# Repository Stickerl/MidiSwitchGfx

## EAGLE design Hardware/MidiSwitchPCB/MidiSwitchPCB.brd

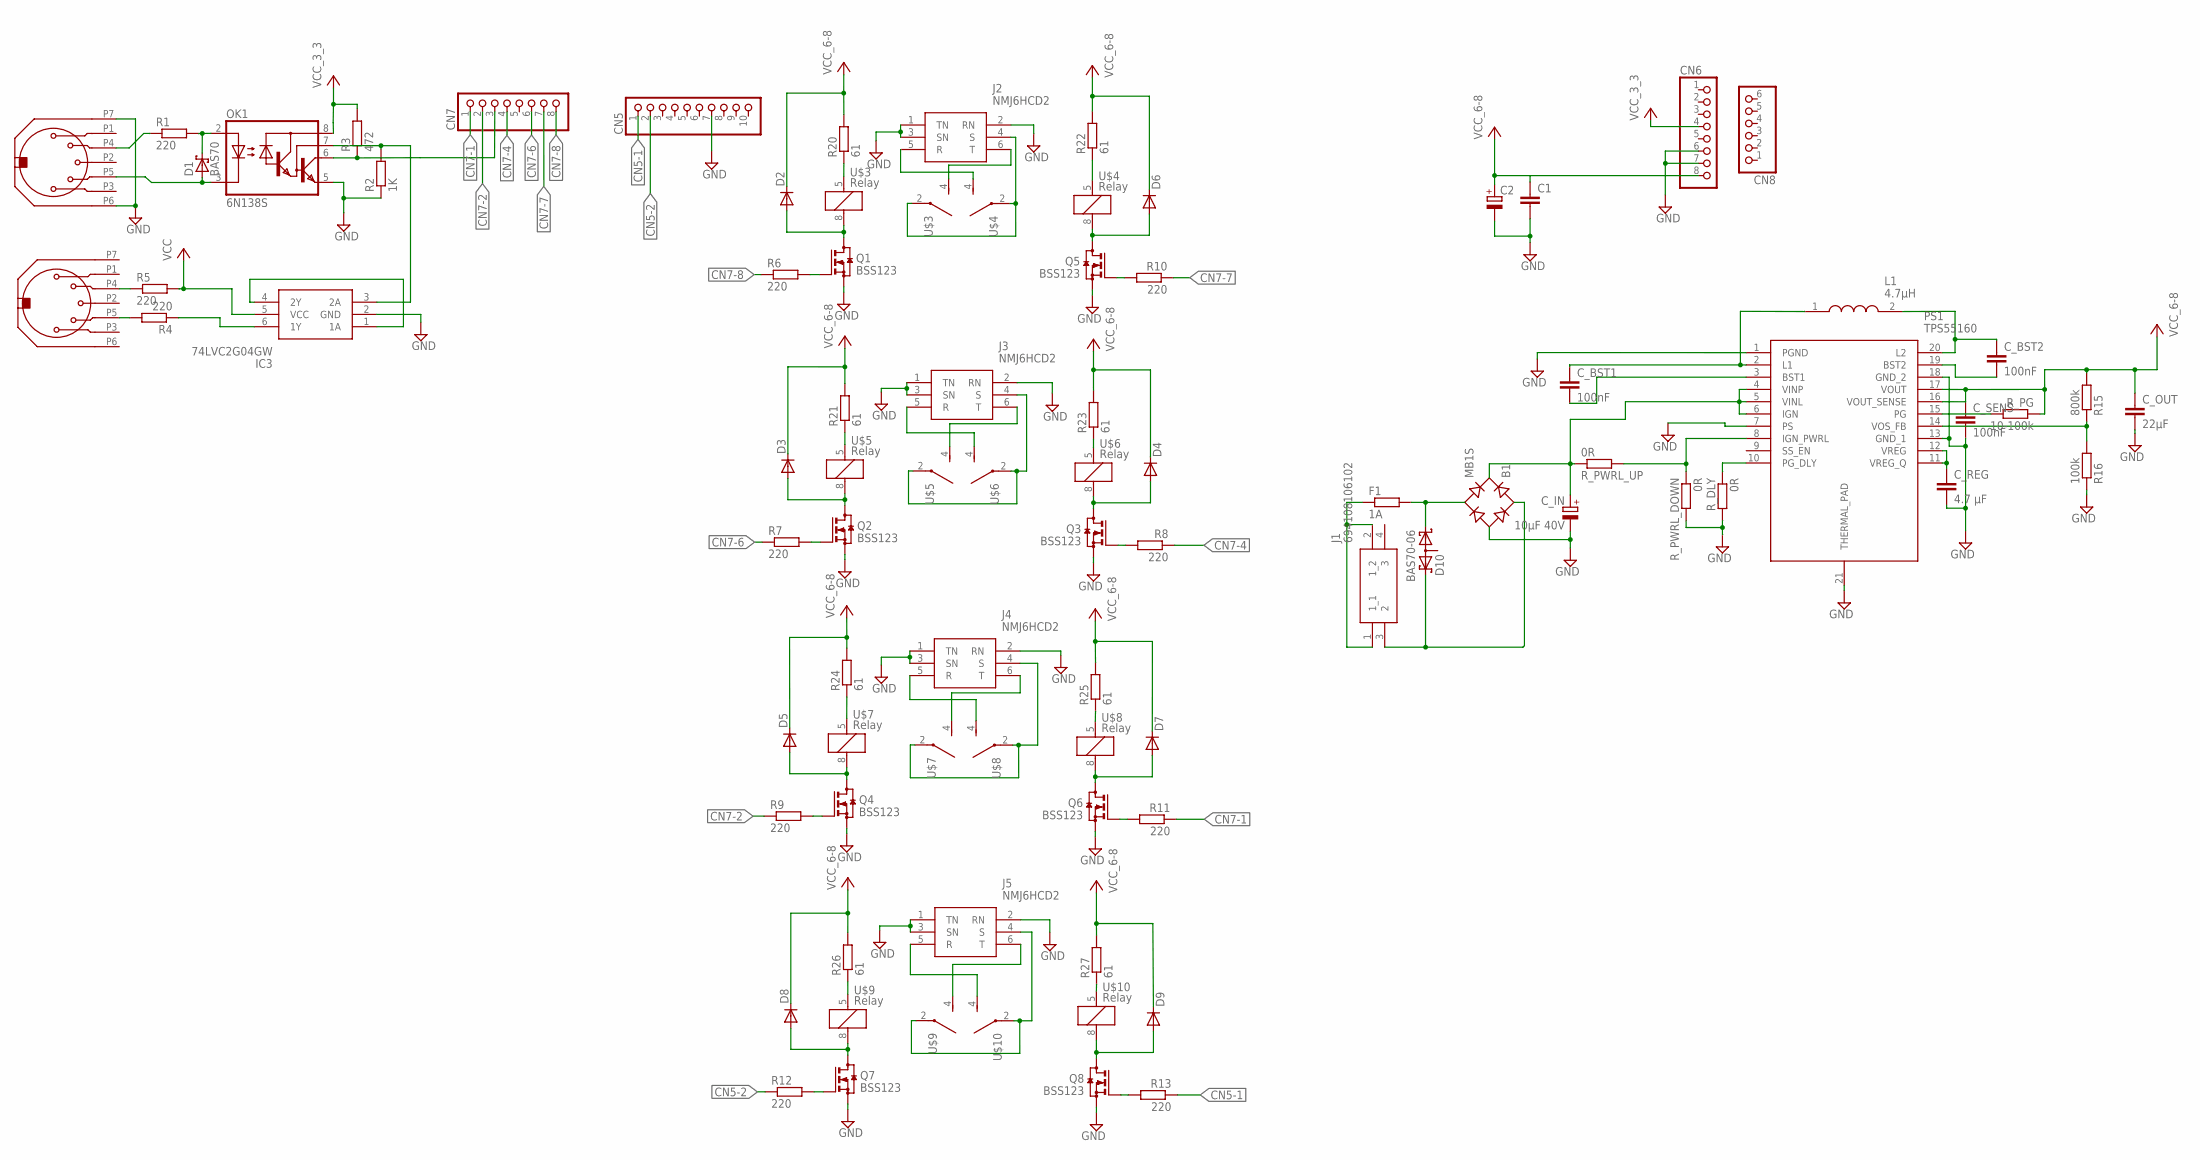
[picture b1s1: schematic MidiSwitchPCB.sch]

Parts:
B1: MB1S; SOIC-4
C1: C-EUC0603; C0603
C2: CPOL-EU153CLV-1012; 153CLV-1012
CN5: PINHD-1X10; 1X10
CN6, CN7: PINHD-1X8; 1X08
CN8: PINHD-1X6; 1X06
C_BST1, C_BST2: 100nF; C1206
C_IN: 10µF 40V; 153CLV-0605
C_OUT: 22µF; C1210K
C_REG: 4.7 µF; C0805
C_SENS: 100nF; C0603
D1: BAS70; SOT23
D2, D3, D4, D5, D6, D7, D8, D9: DIODE-DO-214AC; DO-214AC
D10: BAS70-06; SOT23
F1: 1A; R0603
IC3: 74LVC2G04GW; SOT65P210X110-6N
J1: 694108106102
J2, J3, J4, J5: NMJ6HCD2
L1: 4.7µH; NRS8030T4R7MJGJ
MIDI-IN: MIDI_CONNECTOR; MIDI_CONNECTOR_PAC
MIDI-THRU: MIDI_CONNECTOR; MIDI_CONNECTOR_PAC
OK1: 6N138S; DIL8-SMD
PS1: TPS55160; SOP65P640X120-21N
Q1, Q2, Q3, Q4, Q5, Q6, Q7, Q8: BSS123; SOT23
R1, R4, R5, R6, R7, R8, R9, R10, R11, R12, R13: 220; R0603
R2: 1K; R0603
R3: 472; R0603
R15: 800k; R0603
R16: 100k; R0603
R20, R21, R22, R23, R24, R25, R26, R27: 61; R0603
R_DLY: 0R; R0603
R_PG: 10-100k; R0603
R_PWRL_DOWN: 0R; R0603
R_PWRL_UP: 0R; R0603
U$3, U$4, U$5, U$6, U$7, U$8, U$9, U$10: Relay; G6L1FTRDC5

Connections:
CN5-1: CN5.1, R13.1
CN5-2: CN5.2, R12.1
CN7-1: CN7.1, R11.1
CN7-2: CN7.2, R9.1
CN7-4: CN7.4, R8.1
CN7-6: CN7.6, R7.1
CN7-7: CN7.7, R10.1
CN7-8: CN7.8, R6.1
GND: B1.-, C1.2, C2.-, CN5.7, CN6.6, CN6.7, C_IN.-, C_OUT.2, C_REG.2, C_SENS.2, IC3.2 (GND), J2.1 (TN), J2.2 (RN), J2.3 (SN), J3.1 (TN), J3.2 (RN), J3.3 (SN), J4.1 (TN), J4.2 (RN), J4.3 (SN), J5.1 (TN), J5.2 (RN), J5.3 (SN), MIDI-IN.P6, MIDI-IN.P7, OK1.5 (GND), PS1.1 (PGND), PS1.7 (PS), PS1.13 (GND_1), PS1.18 (GND_2), PS1.21 (THERMAL_PAD), Q1.2 (S), Q2.2 (S), Q3.2 (S), Q4.2 (S), Q5.2 (S), Q6.2 (S), Q7.2 (S), Q8.2 (S), R2.1, R16.1, R_DLY.2, R_PWRL_DOWN.2
MIDI_RX: IC3.3 (2A), OK1.7 (VB), R2.2
unnamed: IC3.1 (1A), IC3.4 (2Y)
unnamed: J2.6 (T), U$3.4 (S)
unnamed: MIDI-IN.P4, R1.1
unnamed: J2.5 (R), U$4.4 (S)
unnamed: MIDI-THRU.P4, R5.1
unnamed: J3.6 (T), U$5.4 (S)
unnamed: D1.3 (C), OK1.2 (A), R1.2
unnamed: D1.1 (A), MIDI-IN.P5, OK1.3 (C)
unnamed: CN7.3, OK1.6 (VO), R3.1
unnamed: MIDI-THRU.P5, R4.2
unnamed: IC3.6 (1Y), R4.1
unnamed: D2.A, Q1.3 (D), U$3.8 (2)
unnamed: D3.A, Q2.3 (D), U$5.8 (2)
unnamed: Q1.1 (G), R6.2
unnamed: Q2.1 (G), R7.2
unnamed: D4.A, Q3.3 (D), U$6.8 (2)
unnamed: Q3.1 (G), R8.2
unnamed: J3.5 (R), U$6.4 (S)
unnamed: D6.A, Q5.3 (D), U$4.8 (2)
unnamed: Q5.1 (G), R10.2
unnamed: J4.6 (T), U$7.4 (S)
unnamed: J3.4 (S), U$5.2, U$6.2
unnamed: D5.A, Q4.3 (D), U$7.8 (2)
unnamed: Q4.1 (G), R9.2
unnamed: D7.A, Q6.3 (D), U$8.8 (2)
unnamed: Q6.1 (G), R11.2
unnamed: J4.5 (R), U$8.4 (S)
unnamed: J5.6 (T), U$9.4 (S)
unnamed: J5.5 (R), U$10.4 (S)
unnamed: J4.4 (S), U$7.2, U$8.2
unnamed: D8.A, Q7.3 (D), U$9.8 (2)
unnamed: Q7.1 (G), R12.2
unnamed: D9.A, Q8.3 (D), U$10.8 (2)
unnamed: B1.~2 (AC2), D10.1 (K1), F1.2
unnamed: B1.~1 (AC1), D10.2 (K2), J1.3 (2)
unnamed: J2.4 (S), U$3.2, U$4.2
unnamed: Q8.1 (G), R13.2
unnamed: F1.1, J1.1 (1_1), J1.2 (1_2)
unnamed: B1.+, C_IN.+, PS1.4 (VINP), PS1.5 (VINL), PS1.6 (IGN), R_PWRL_UP.1
unnamed: J5.4 (S), U$9.2, U$10.2
unnamed: PS1.10 (PG_DLY), R_DLY.1
unnamed: PS1.14 (VOS_FB), R15.1, R16.2
unnamed: C_BST2.1, L1.2, PS1.20 (L2)
unnamed: PS1.15 (PG), R_PG.2
unnamed: R23.1, U$6.5 (1)
unnamed: C_BST2.2, PS1.19 (BST2)
unnamed: C_BST1.1, L1.1, PS1.2 (L1)
unnamed: C_BST1.2, PS1.3 (BST1)
unnamed: C_REG.1, PS1.11 (VREG_Q), PS1.12 (VREG)
unnamed: PS1.8 (IGN_PWRL), R_PWRL_DOWN.1, R_PWRL_UP.2
unnamed: R20.1, U$3.5 (1)
unnamed: R22.1, U$4.5 (1)
unnamed: R21.1, U$5.5 (1)
unnamed: R27.1, U$10.5 (1)
unnamed: R24.1, U$7.5 (1)
unnamed: R25.1, U$8.5 (1)
unnamed: R26.1, U$9.5 (1)
VCC_3_3: CN6.4, IC3.5 (VCC), OK1.8 (VCC), R3.2, R5.2
VCC_6-8: C1.1, C2.+, CN6.8, C_OUT.1, C_SENS.1, D2.C, D3.C, D4.C, D5.C, D6.C, D7.C, D8.C, D9.C, PS1.16 (VOUT_SENSE), PS1.17 (VOUT), R15.2, R20.2, R21.2, R22.2, R23.2, R24.2, R25.2, R26.2, R27.2, R_PG.1

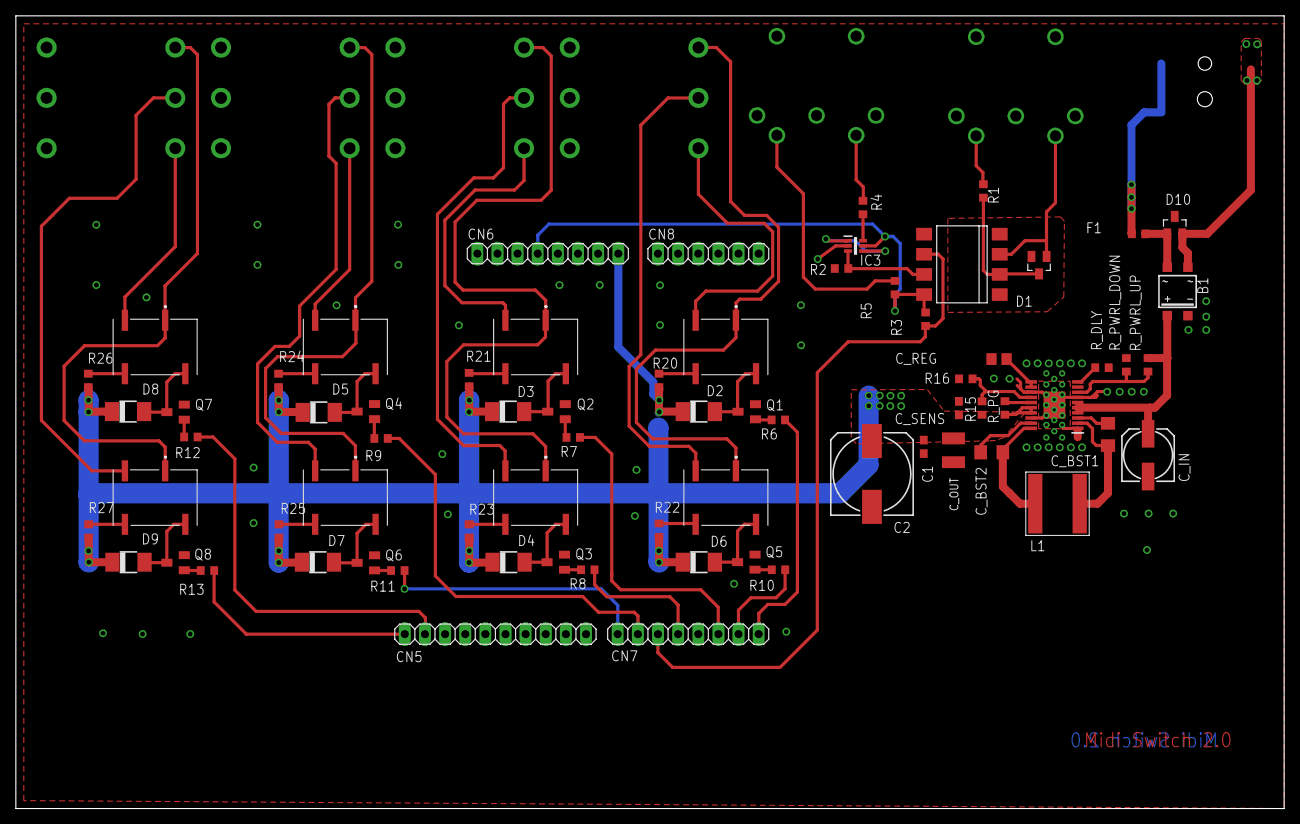
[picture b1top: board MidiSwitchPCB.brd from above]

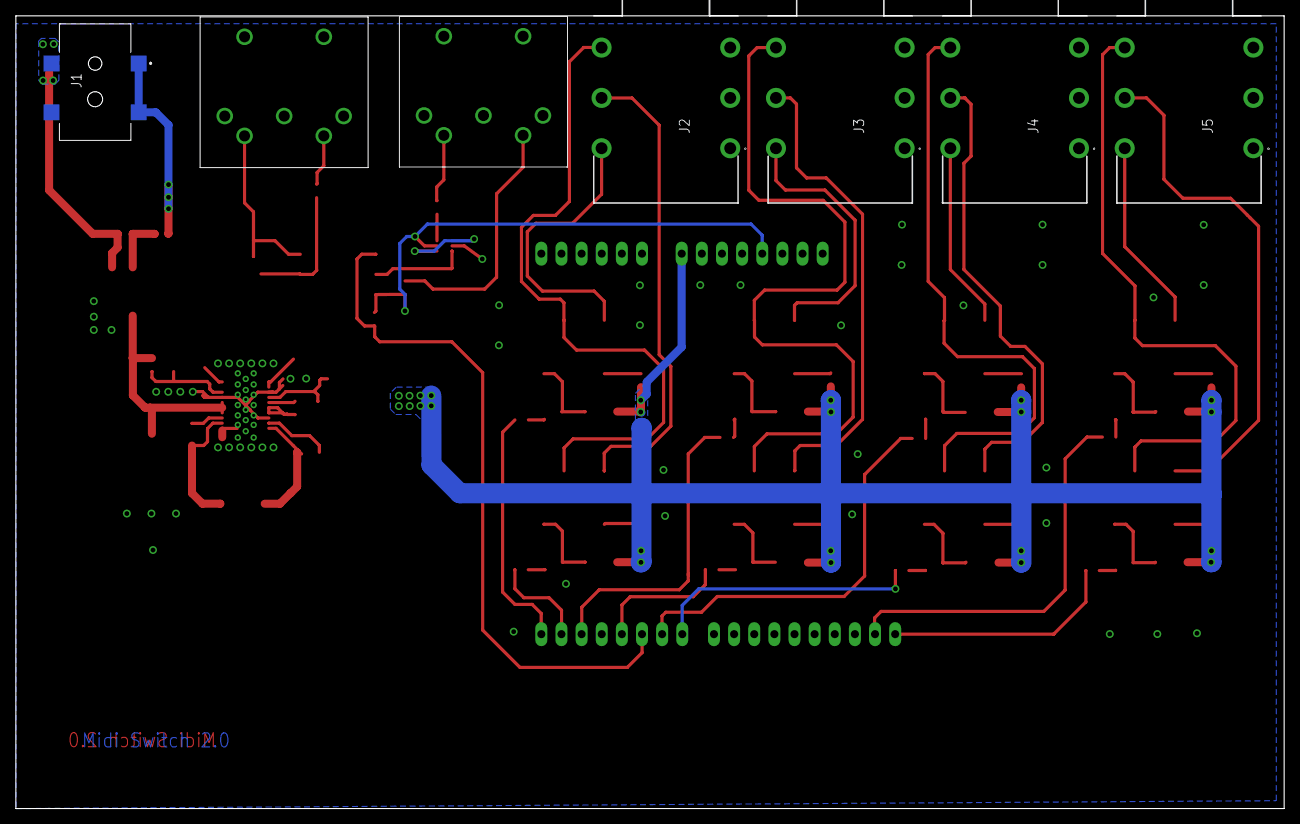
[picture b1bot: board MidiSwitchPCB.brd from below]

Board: 2 copper layers, 160.0 x 100.0 mm, 78 parts (7 on the bottom side), 69 nets.

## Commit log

2018-08-15 Added the project workspace.
2018-08-16 removed unused projects out of the WS
2018-08-17 Added ringbuffer class and a first version of UartIrqBased.
2018-08-18 Added MidiDecoder class
2018-08-26 added flash and configuration manager modules both are currently not functional
2018-08-27 Changed the RingBuffer to a template so that there is no need to allocate the buffer memory outside of the class. Continued the work on UartIrqBased
2018-08-27 added uart interface
2018-09-01 implemented the most of the configuration manager except the GUI updating and the teach function.
2018-09-07 added uart_irqs and a callback interface
2018-09-13 Implemented uart irq class and added a init struct for uart class
2018-09-13 connected midi data in the model to the gui
2018-09-13 added uart interrupt registration interface
2018-09-14 added midi task
2018-09-14 uart irq partly implemented. To be continued
2018-09-15 added digital output class
2018-09-21 Removed config number from the config page screen
2018-10-03 Cleaned up the project settings
2018-10-12 added some documentation
2018-10-12 Implementation of UART module
2018-10-12 Matthias Eclicks settings
2018-10-19 added midi_task
2018-10-19 Add information which pins, that are connected to pin headers, can be controlled by UART-modules
2018-10-19 commit .metadata to make git happy, so that I can push my changes
2018-11-09 added gui_queue for inter process communication, global defines and pc interface task. implemented callbacks for next and prev button
2018-11-09 fixed typo in config_manager
2018-11-16 Fixed off by one error in the GUI and started with the flash.
2018-11-23 hier könnte ihre Werbung stehen ;)
2018-11-30 added function definitions for the flash module
2018-11-30 implemented determineActiveSector method. It is currently not tested!
2018-11-30 implemented some functions in flash.cpp. You will like them. No Wait! You won't :) :) :)
2019-01-04 clean up NVM functions
2019-01-04 implemented store and copyToNvm as well as getFreeMemory function
2019-01-11 implemented the store method. copyToNvm doesn't work correctly.
2019-01-11 wadde hadde dudde da?
2019-01-13 finished the implementation of copyToNvm and store function.
2019-01-19 added a generic ring buffer implementation. continued debugging the store function of the flash module
2019-02-01 got the relocation working
2019-02-08 Working test bench for nvm class, storing and relocating 3 frames tested. Die scheiße geht!!!
2019-03-01 Flash module finished, debug code not dead :(
2019-03-01 removed debug code
2019-03-15 started with the implementation of the communication between GUI and backend. The model needs some rework now.
2019-03-23 continued connecting GUI and backend
2019-04-05 startet implementing a numeric keyboard
2019-04-06 continued OutputCfg and gui communication implementation. Added touch_event_extension class which is not tested so far.
2019-04-07 enhanced touch_event_extension class to make text areas editable by the numericKeyboard and continued connecting GUI to backend
2019-04-19 started filling the global config view with live. added some files of the framework which should have been part of the most recent update.
2019-04-26 continued connecting global config view to the backend
2019-04-26 Current GUI fully (except Teach button) connected to backend.
2019-05-24 added first version of the schematic.
2019-06-07 added output pins and tested midi interpretation as well as frames for hterm
2019-06-07 fixed a little bug regarding control change commands
2019-06-19 continued schematic designing
2019-06-19 added most of the power supply.
2019-07-12 created the part list and selected some devices
2019-07-19 added pcb
2019-07-19 added inductor to part list, Mann!
2019-07-19 added switching capacitor to part list (changed cap-package in layout from 0603 to 1206)
2019-07-19 added some links to partlist
2019-08-02 added some part libraries
2019-08-09 continued searching parts
2019-08-16 finished part selection
2019-08-30 changed some device packages
2019-08-30 placed devices on the layout
2019-09-06 Finished device placement and added a fuse as well as an ESD diode
2019-09-06 started routing
2019-09-13 continued layout design. The pinheaders are unfortunately connected on the wrong pcb side.
2019-09-20 Continued Layout editing.
2019-10-04 checked the footprints
2019-10-06 Changed PCB size to 160 x 100
2019-10-06 Created manufacturing documents
2019-11-23 Started reworking the layout before ordering it
2019-11-29 finished layout reworking
2019-11-29 added gerber files
2020-01-10 fixed some wrong pin configurations and the generic_ring_buffer implementation
2020-01-10 Debugged pin configuration causing device to be stuck in initialization. Debug code needs to be removed. Reverted pin config to previous pin config. Bug needs to be fixed in HW
